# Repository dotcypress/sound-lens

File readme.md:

# Sound Lens
PDM microphones breakout board.

## Resources

- [Schematics](pcb/SoundLens.pdf)
- [Gerber files](pcb/fab)

## License

Licensed under either of

- Apache License, Version 2.0 ([LICENSE-APACHE](LICENSE-APACHE) or
  http://www.apache.org/licenses/LICENSE-2.0)
- MIT license ([LICENSE-MIT](LICENSE-MIT) or http://opensource.org/licenses/MIT)

at your option.

### Contribution

Unless you explicitly state otherwise, any contribution intentionally submitted
for inclusion in the work by you, as defined in the Apache-2.0 license, shall be
dual licensed as above, without any additional terms or conditions.

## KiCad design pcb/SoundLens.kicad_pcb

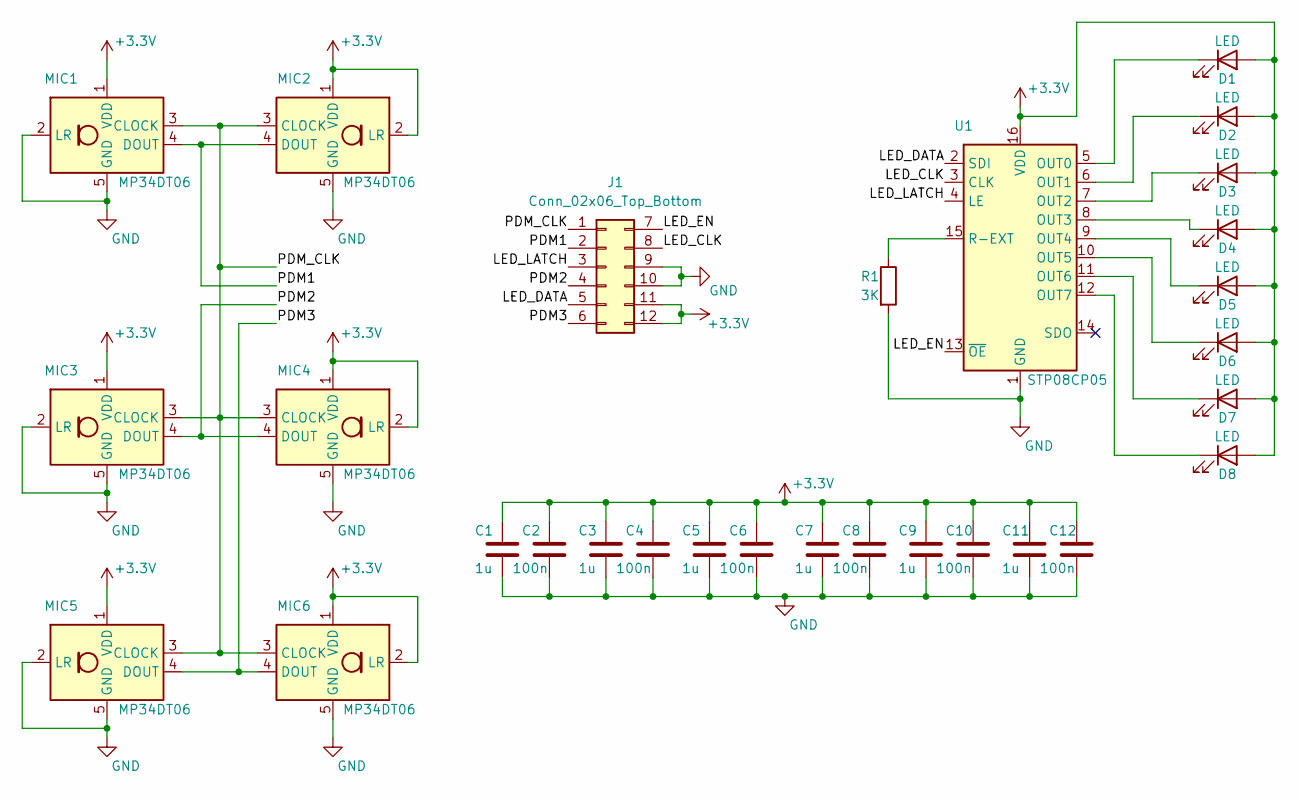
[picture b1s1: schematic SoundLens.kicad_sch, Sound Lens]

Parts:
C1, C3, C5, C7, C9, C11: 1u; R_0603_1608Metric
C2, C4, C6, C8, C10, C12: 100n; R_0603_1608Metric
D1, D2, D3, D4, D5, D6, D7, D8: LED; LED_0603_1608Metric
J1: Conn_02x06_Top_Bottom; PinHeader_2x06_P2.54mm_Vertical
MIC1, MIC2, MIC3, MIC4, MIC5, MIC6: MP34DT06; MP34DT06J
R1: 3K; R_0603_1608Metric
U1: STP08CP05; TSSOP-16_4.4x5mm_P0.65mm

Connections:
+3V3: C1.1, C2.1, C3.1, C4.1, C5.1, C6.1, C7.1, C8.1, C9.1, C10.1, C11.1, C12.1, D1.2 (A), D2.2 (A), D3.2 (A), D4.2 (A), D5.2 (A), D6.2 (A), D7.2 (A), D8.2 (A), J1.11, J1.12, MIC1.1 (VDD), MIC2.1 (VDD), MIC2.2 (LR), MIC3.1 (VDD), MIC4.1 (VDD), MIC4.2 (LR), MIC5.1 (VDD), MIC6.1 (VDD), MIC6.2 (LR), U1.16 (VDD)
/LED_CLK: J1.8, U1.3 (CLK)
/LED_DATA: J1.5, U1.2 (SDI)
/LED_EN: J1.7, U1.13 (~OE)
/LED_LATCH: J1.3, U1.4 (LE)
/PDM1: J1.2, MIC1.4 (DOUT), MIC2.4 (DOUT)
/PDM2: J1.4, MIC3.4 (DOUT), MIC4.4 (DOUT)
/PDM3: J1.6, MIC5.4 (DOUT), MIC6.4 (DOUT)
/PDM_CLK: J1.1, MIC1.3 (CLOCK), MIC2.3 (CLOCK), MIC3.3 (CLOCK), MIC4.3 (CLOCK), MIC5.3 (CLOCK), MIC6.3 (CLOCK)
GND: C1.2, C2.2, C3.2, C4.2, C5.2, C6.2, C7.2, C8.2, C9.2, C10.2, C11.2, C12.2, J1.9, J1.10, MIC1.2 (LR), MIC1.5 (GND), MIC2.5 (GND), MIC3.2 (LR), MIC3.5 (GND), MIC4.5 (GND), MIC5.2 (LR), MIC5.5 (GND), MIC6.5 (GND), R1.2, U1.1 (GND)
unnamed: D1.1 (K), U1.5 (OUT0)
unnamed: D2.1 (K), U1.6 (OUT1)
unnamed: D3.1 (K), U1.7 (OUT2)
unnamed: D4.1 (K), U1.8 (OUT3)
unnamed: D5.1 (K), U1.9 (OUT4)
unnamed: D6.1 (K), U1.10 (OUT5)
unnamed: D7.1 (K), U1.11 (OUT6)
unnamed: D8.1 (K), U1.12 (OUT7)
unnamed: R1.1, U1.15 (R-EXT)

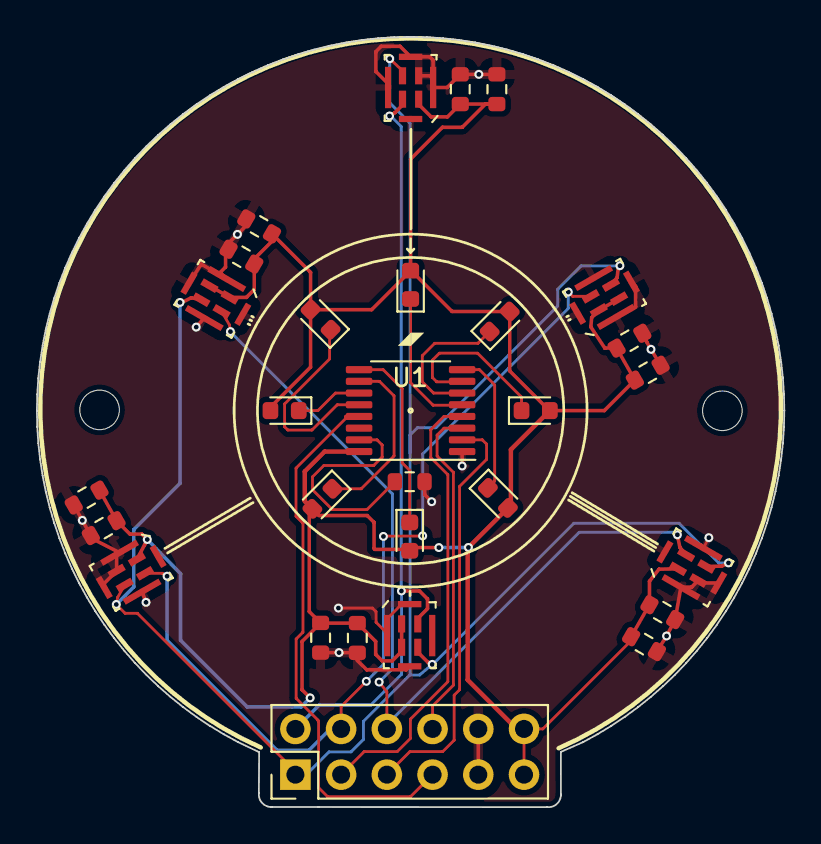
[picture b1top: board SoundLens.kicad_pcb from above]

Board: 2 copper layers, 41.5 x 42.8 mm, 29 parts (0 on the bottom side), 19 nets.

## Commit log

2021-02-23 rev 0.1
2021-03-24 add readme
